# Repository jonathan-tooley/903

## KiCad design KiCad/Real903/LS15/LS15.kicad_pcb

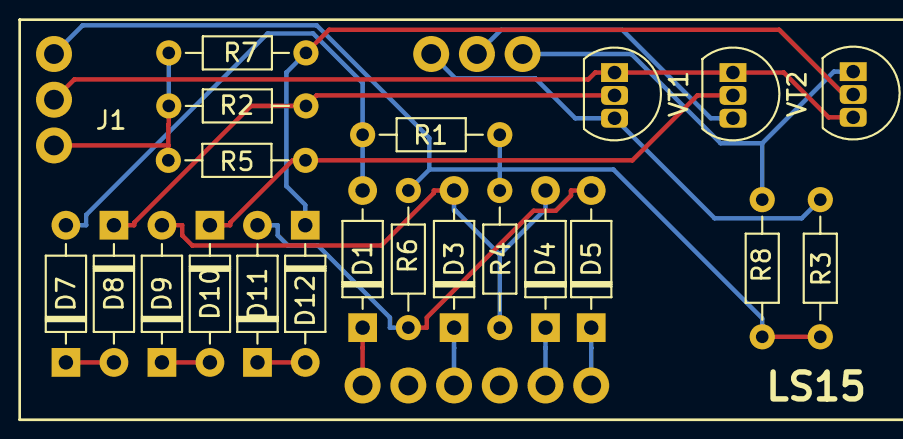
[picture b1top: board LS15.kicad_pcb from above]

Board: 2 copper layers, 22 parts (0 on the bottom side), 19 nets.

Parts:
D1, D3, D4, D5, D7, D8, D9, D10, D11, D12: 1N4148; D_DO-35_SOD27_P7.62mm_Horizontal
J1: LSAConnect; LSA
R1, R6: 1k; R_Axial_DIN0204_L3.6mm_D1.6mm_P7.62mm_Horizontal
R2, R7: 10k; R_Axial_DIN0204_L3.6mm_D1.6mm_P7.62mm_Horizontal
R3, R8: 390R; R_Axial_DIN0204_L3.6mm_D1.6mm_P7.62mm_Horizontal
R4: 2.2k; R_Axial_DIN0204_L3.6mm_D1.6mm_P7.62mm_Horizontal
R5: 22k; R_Axial_DIN0204_L3.6mm_D1.6mm_P7.62mm_Horizontal
VT1: BC548; TO-92L_InlineCBE
VT2, VT3: BC548; TO-92L_Inline

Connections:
0v: J1.22, VT1.3, VT2.3, VT3.3
1: D1.1, J1.1
3: D3.1, J1.3
5: D4.1, J1.5
6: D5.1, J1.6
11: J1.11, R3.1, VT1.1
12: J1.12, VT2.1
13: J1.13, R8.1, VT3.1
+6v: J1.21, R1.1, R3.2, R4.1, R6.1, R8.2
-6v: J1.23, R2.2, R5.2, R7.2
unnamed: D1.2, D7.2, R1.2
unnamed: D3.2, D4.2, D9.2, R4.2
unnamed: D7.1, D8.2
unnamed: D8.1, R2.1, VT1.2
unnamed: D10.1, R5.1, VT2.2
unnamed: D9.1, D10.2
unnamed: D11.1, D12.2
unnamed: D5.2, D11.2, R6.2
unnamed: D12.1, R7.1, VT3.2

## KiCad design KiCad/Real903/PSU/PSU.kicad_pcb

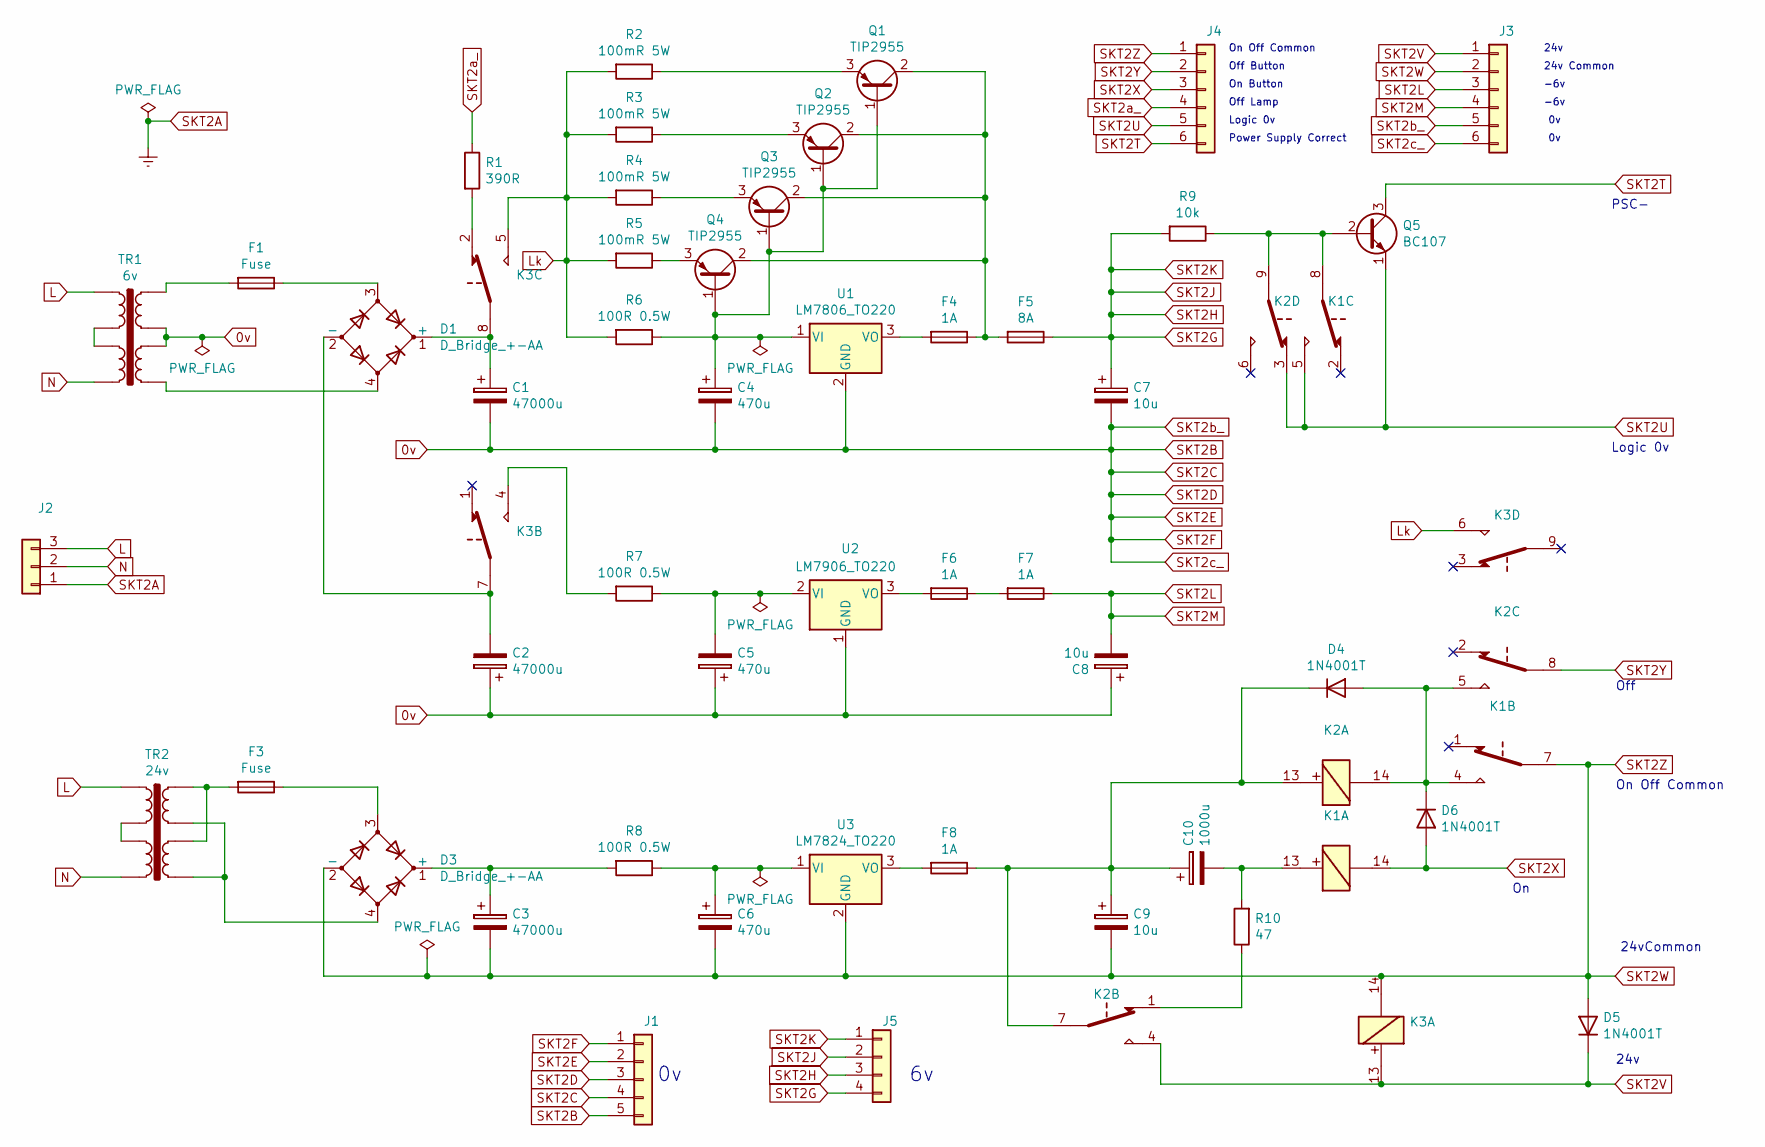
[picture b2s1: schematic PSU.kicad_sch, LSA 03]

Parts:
C1, C2, C3: 47000u; CP_Radial_D35.0mm_P10.00mm_SnapIn
C4, C5, C6: 470u; CP_Radial_D8.0mm_P3.50mm
C7, C8, C9: 10u; CP_Radial_D4.0mm_P1.50mm
C10: 1000u; CP_Radial_D12.5mm_P5.00mm
D1, D3: D_Bridge_+-AA; Diode_Bridge_Vishay_GBU
D4, D5, D6: 1N4001T; D_DO-41_SOD81_P7.62mm_Horizontal
F1, F3: Fuse; TerminalBlock_MetzConnect_Type171_RT13702HBWC_1x02_P7.50mm_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
F4, F6, F7, F8: 1A; TerminalBlock_MetzConnect_Type171_RT13702HBWC_1x02_P7.50mm_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
F5: 8A; TerminalBlock_MetzConnect_Type171_RT13702HBWC_1x02_P7.50mm_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
J1: TerminalBlock_MetzConnect_Type171_RT13705HBWC_1x05_P7.50mm_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
J2: TerminalBlock_MetzConnect_Type171_RT13703HBWC_1x03_P7.50mm_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
J3, J4: TerminalBlock_MetzConnect_Type171_RT13706HBWC_1x06_P7.50mm_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
J5: TerminalBlock_MetzConnect_Type171_RT13704HBWC_1x04_P7.50mm_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
K1, K2, K3: Relay55.13
Q1, Q2, Q3, Q4: TIP2955; TO-218-3_Vertical
Q5: BC107; TO-92L_Inline
R1: 390R; R_Axial_DIN0204_L3.6mm_D1.6mm_P7.62mm_Horizontal
R2, R3, R4, R5: 100mR 5W; R_Axial_Power_L25.0mm_W6.4mm_P27.94mm
R6, R7, R8: 100R 0.5W; R_Axial_DIN0207_L6.3mm_D2.5mm_P2.54mm_Vertical
R9: 10k; R_Axial_DIN0204_L3.6mm_D1.6mm_P7.62mm_Horizontal
R10: 47; R_Axial_DIN0204_L3.6mm_D1.6mm_P7.62mm_Horizontal
TR1: 6v; FL526Transformer
TR2: 24v; FL3024Transformer
U1: LM7806_TO220; TO-220-3_Vertical
U2: LM7906_TO220; TO-220-3_Vertical
U3: LM7824_TO220; TO-220-3_Vertical

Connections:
0v: C1.2, C2.1, C4.2, C5.1, C7.2, C8.1, J1.1, J1.2, J1.3, J1.4, J1.5, J3.5, J3.6, TR1.6, TR1.7, U1.2 (GND), U2.1 (GND)
L: J2.3, TR1.1, TR2.1
Lk: K3.5, K3.6, R2.2, R3.2, R4.2, R5.2, R6.2
N: J2.2, TR1.4, TR2.4
unnamed: C1.1, D1.1 (+), K3.8
unnamed: C2.2, D1.2 (-), K3.7
unnamed: C3.1, D3.1 (+), R8.2
unnamed: C4.1, Q1.1 (B), Q2.1 (B), Q3.1 (B), Q4.1 (B), R6.1, U1.1 (VI)
unnamed: C5.2, R7.1, U2.2 (VI)
unnamed: C6.1, R8.1, U3.1 (VI)
unnamed: C9.1, C10.1, D4.1 (K), F8.1, K2.7, K2.13
unnamed: C10.2, K1.13, R10.2
unnamed: D1.3, F1.1
unnamed: D3.3, F3.1
unnamed: D3.4, TR2.5, TR2.7
unnamed: D4.2 (A), D6.1 (K), K1.4, K2.5, K2.14
unnamed: F1.2, TR1.8
unnamed: F3.2, TR2.6, TR2.8
unnamed: F4.1, F5.2, Q1.2 (C), Q2.2 (C), Q3.2 (C), Q4.2 (C)
unnamed: F4.2, U1.3 (VO)
unnamed: F6.1, F7.2
unnamed: F6.2, U2.3 (VO)
unnamed: F8.2, U3.3 (VO)
unnamed: K1.8, K2.9, Q5.2 (B), R9.1
unnamed: K2.1, R10.1
unnamed: K3.2, R1.2
unnamed: K3.4, R7.2
unnamed: Q1.3 (E), R2.1
unnamed: Q2.3 (E), R3.1
unnamed: Q3.3 (E), R4.1
unnamed: Q4.3 (E), R5.1
unnamed: TR1.2, TR1.3
unnamed: TR2.2, TR2.3
SKT2G: C7.1, F5.1, J5.1, J5.2, J5.3, J5.4, R9.2
SKT2L: C8.2, F7.1, J3.3, J3.4
SKT2T: J4.6, Q5.3 (C)
SKT2U: J4.5, K1.5, K2.3, Q5.1 (E)
SKT2V: D5.1 (K), J3.1, K2.4, K3.13
SKT2W: C3.2, C6.2, C9.2, D3.2 (-), D5.2 (A), J3.2, J4.1, K1.7, K3.14, U3.2 (GND)
SKT2X: D6.2 (A), J4.3, K1.14
SKT2Y: J4.2, K2.8
SKT2a_: J4.4, R1.1

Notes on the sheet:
-6v
24v
On Off Common
PSC-
Off Lamp
Logic 0v
Power Supply Correct
Off Button
24vCommon
On Button
24v Common
Off

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
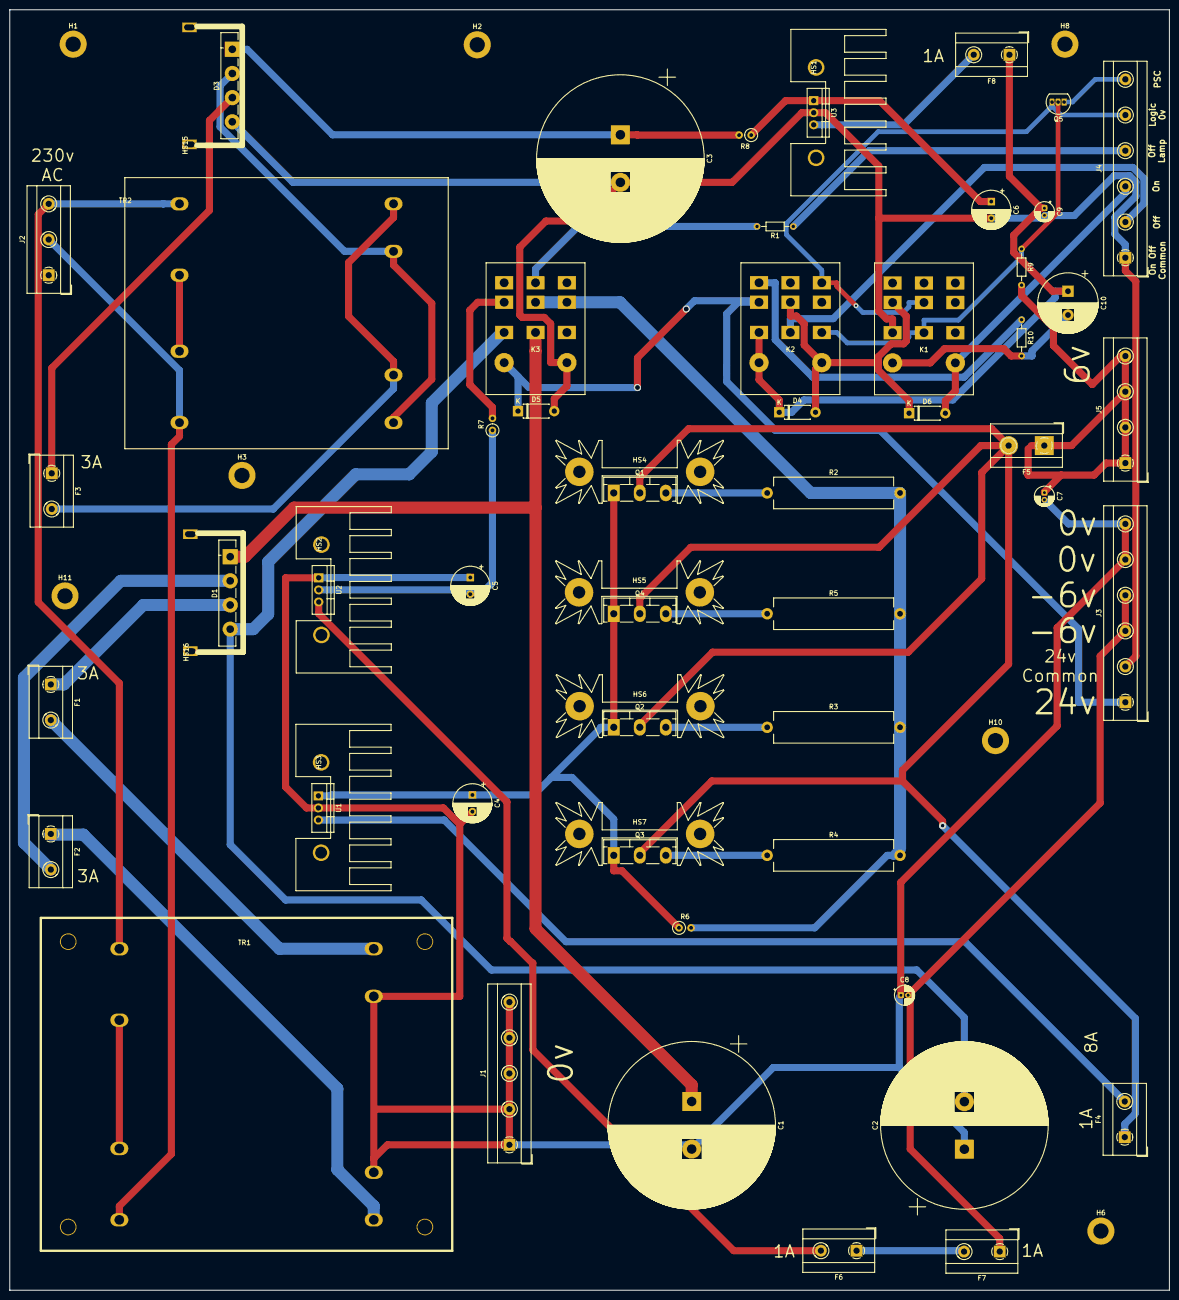
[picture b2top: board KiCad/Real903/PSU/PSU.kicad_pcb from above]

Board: 2 copper layers, 243.8 x 269.2 mm, 67 parts (0 on the bottom side), 44 nets.

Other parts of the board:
F2: Fuse; TerminalBlock_MetzConnect_Type171_RT13702HBWC_1x02_P7.50mm_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
H1, H2, H3, H6, H8, H10, H11: MountingHole_3.2mm_M3_ISO7380_Pad
HS1, HS2, HS3: Heatsink
HS4, HS5, HS6, HS7: Heatsink_TO247
HS15, HS16: Heatsink 712-4241

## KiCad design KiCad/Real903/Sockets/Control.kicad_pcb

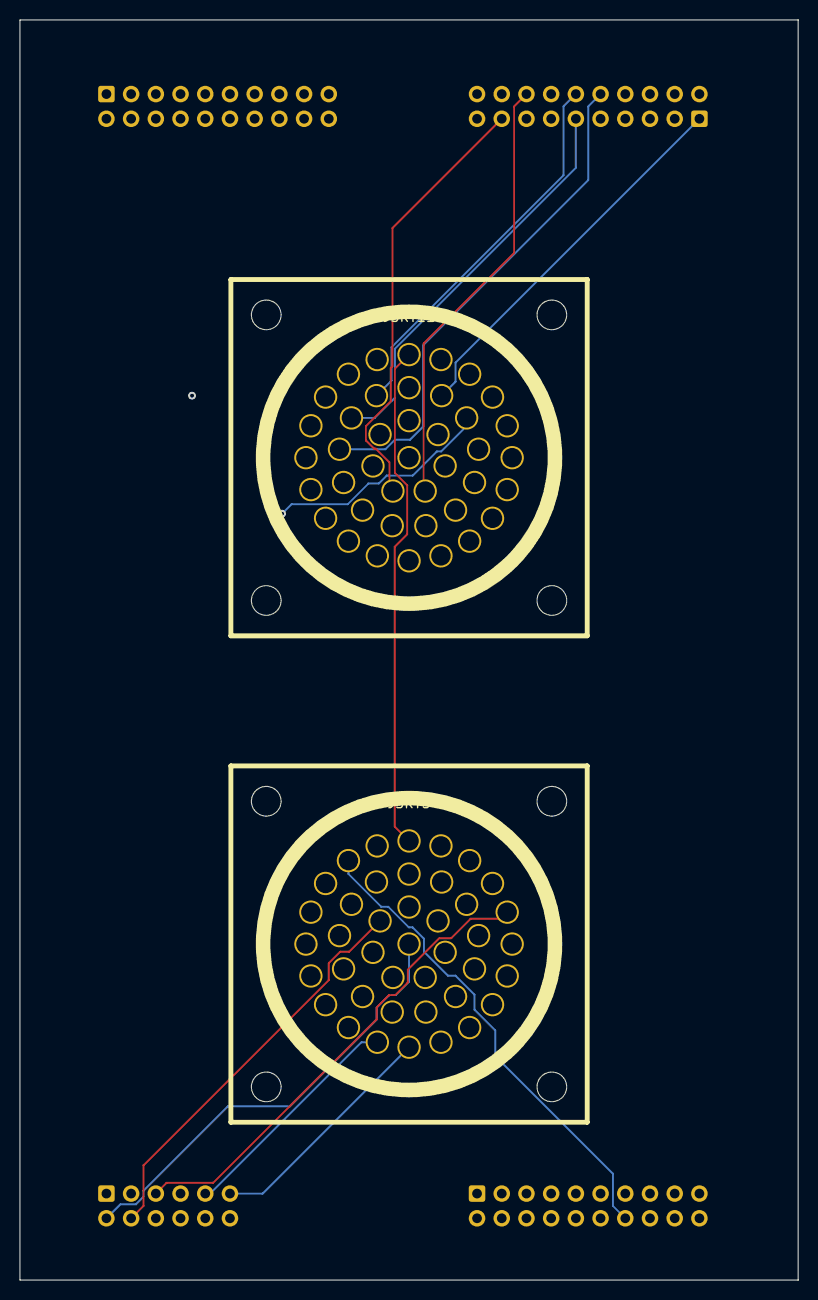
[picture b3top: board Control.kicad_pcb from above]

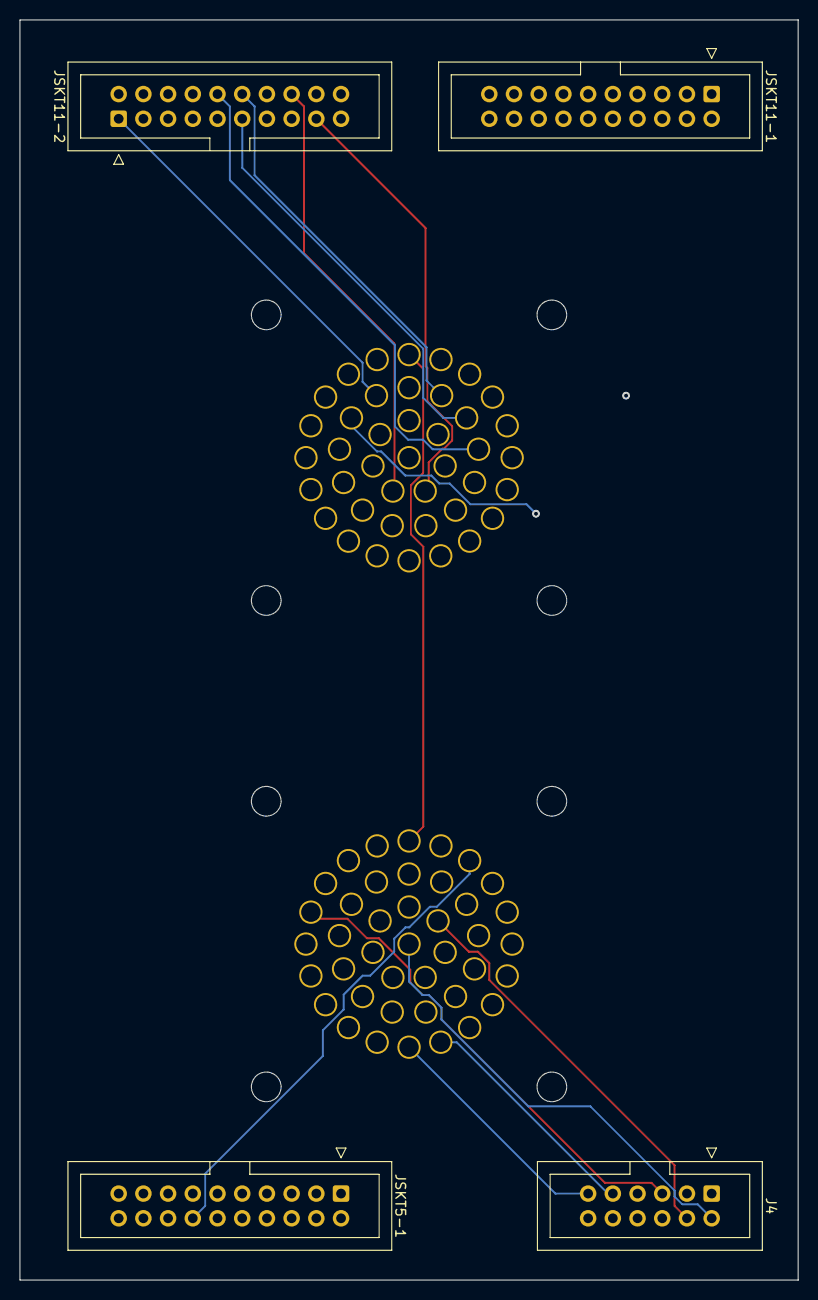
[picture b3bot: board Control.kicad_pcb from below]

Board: 4 copper layers, 80.0 x 129.5 mm, 6 parts (4 on the bottom side), 63 nets.

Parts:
J4: IDC-Header_2x06_P2.54mm_Vertical
JSKT5, JSKT11: Circ41; MC41
JSKT5-1, JSKT11-1, JSKT11-2: IDC-Header_2x10_P2.54mm_Vertical

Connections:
/Control Unit/0v: J4.6, JSKT5.~q~, JSKT5.~r~, JSKT11.~e~
/Control Unit/#ACTIVE1-1-Y: JSKT5.X, JSKT5-1.12
/Control Unit/#ACTIVE2-1-V: JSKT5.Z, JSKT5-1.10
/Control Unit/#ACTIVE3-1-S: JSKT5.~g~, JSKT5-1.3
/Control Unit/#INT1-3-F: JSKT5.Y, JSKT5-1.11
/Control Unit/#INT2-3-W: JSKT5.~a~, JSKT5-1.9
/Control Unit/#INT3-3-AD: JSKT5.~h~, JSKT5-1.2
/Control Unit/#STOP-2-E: JSKT5.R, JSKT5-1.17
/Control Unit/+6v: J4.4, JSKT5.~s~, JSKT11.~t~
/Control Unit/-6v: J4.2, JSKT5.~t~
/Control Unit/AUDIO-32-14: JSKT5.~p~, JSKT11-2.20
/Control Unit/AUT: J4.8, JSKT11.Z
/Control Unit/AUTO-1-L: JSKT5.~k~, JSKT11-2.18
/Control Unit/Auto-Start: J4.10, JSKT11.~r~, JSKT11.~s~
/Control Unit/CINS-1-J: JSKT5.~b~, JSKT5-1.8
/Control Unit/ENG-1-6: JSKT11.~h~, JSKT11-2.10
/Control Unit/INT1-3-9: JSKT11.W, JSKT11-1.19
/Control Unit/INT2-3-10: JSKT11.X, JSKT11-1.20
/Control Unit/INT3-3-11: JSKT11.Y, JSKT11-2.1
/Control Unit/JUMP-1-M: JSKT5.V, JSKT5-1.14
/Control Unit/ONG-1-7: JSKT11.~f~, JSKT11-2.8
/Control Unit/Off: J4.5, JSKT5.E
/Control Unit/Off-Light: J4.11, JSKT5.L
/Control Unit/On: J4.3, JSKT5.B
/Control Unit/On-Light: J4.9, JSKT5.M
/Control Unit/On-Off-Common: J4.7, JSKT5.C
/Control Unit/PS1-3-E: JSKT11.~m~, JSKT11-2.14
/Control Unit/PS2-3-L: JSKT11.~n~, JSKT11-2.15
/Control Unit/PS3-3-S: JSKT11.~p~, JSKT11-2.16
/Control Unit/RESET-1-24: JSKT11.~j~, JSKT11-2.12
/Control Unit/RESET-2-U: JSKT5.H, JSKT5-1.19
/Control Unit/RESTART-1-C: JSKT5.T, JSKT5-1.16
/Control Unit/W1: JSKT11.B, JSKT11-1.1
/Control Unit/W5: JSKT11.F, JSKT11-1.2
/Control Unit/W6: JSKT11.G, JSKT11-1.3
/Control Unit/W7: JSKT11.H, JSKT11-1.4
/Control Unit/W8: JSKT11.J, JSKT11-1.5
/Control Unit/W9: JSKT11.K, JSKT11-1.6
/Control Unit/W10: JSKT11.L, JSKT11-1.7
/Control Unit/W11: JSKT11.M, JSKT11-1.8
/Control Unit/W12: JSKT11.N, JSKT11-1.9
/Control Unit/W13: JSKT11.P, JSKT11-1.10
/Control Unit/W17: JSKT11.~q~, JSKT11-2.17
/Control Unit/~CINS~-1-8: JSKT5.~c~, JSKT5-1.7
/Control Unit/~CS~-1-H: JSKT5.~e~, JSKT5-1.5
/Control Unit/~ENG~-1-4: JSKT11.~i~, JSKT11-2.11
/Control Unit/~JUMP~-1-11: JSKT5.W, JSKT5-1.13
/Control Unit/~ONG~-1-F: JSKT11.~g~, JSKT11-2.9
/Control Unit/~OS~-1-19: JSKT5.~f~, JSKT5-1.4
/Control Unit/~RESTART~-1-3: JSKT5.U, JSKT5-1.15
/Control Unit/~SMN~-4-7: JSKT5.~i~, JSKT5-1.1
/Control Unit/~STOP~-1-25: JSKT5.P, JSKT5-1.18
/Control Unit/~TCS~-1-AB: JSKT5.~d~, JSKT5-1.6
/Control Unit/~TEST~-1-5: JSKT5.D, JSKT5-1.20
/Control Unit/~W~2: JSKT11.C, JSKT11-1.11
/Control Unit/~W~3: JSKT11.D, JSKT11-1.12
/Control Unit/~W~4: JSKT11.E, JSKT11-1.13
/Control Unit/~W~14: JSKT11.R, JSKT11-1.14
/Control Unit/~W~15: JSKT11.S, JSKT11-1.15
/Control Unit/~W~16: JSKT11.T, JSKT11-1.16
/Control Unit/~W~17: JSKT11.U, JSKT11-1.17
/Control Unit/~W~18: JSKT11.V, JSKT11-1.18
GND: J4.1, J4.12, JSKT5.A, JSKT11.A

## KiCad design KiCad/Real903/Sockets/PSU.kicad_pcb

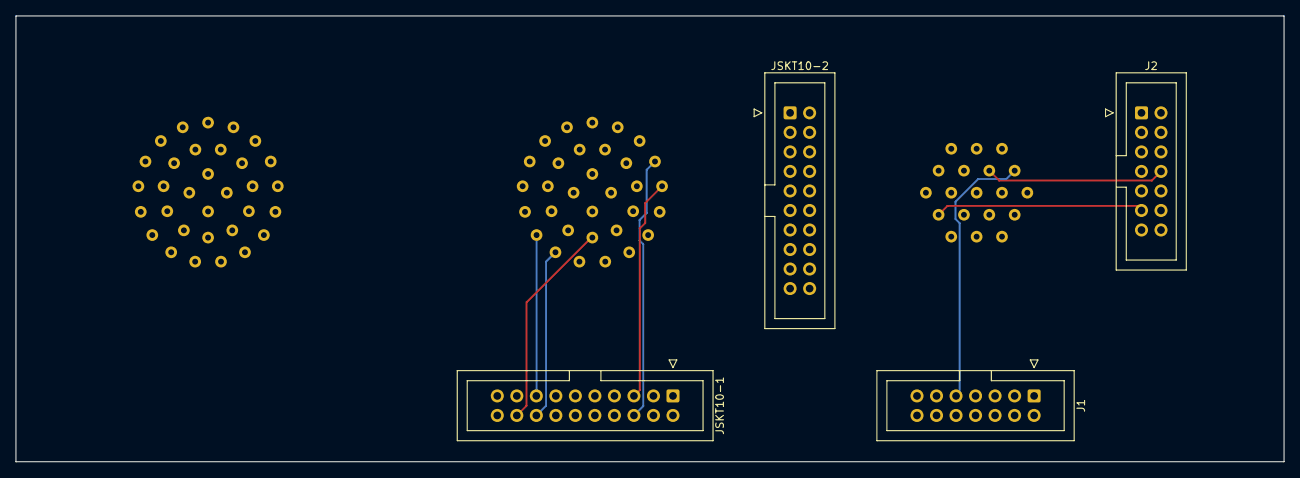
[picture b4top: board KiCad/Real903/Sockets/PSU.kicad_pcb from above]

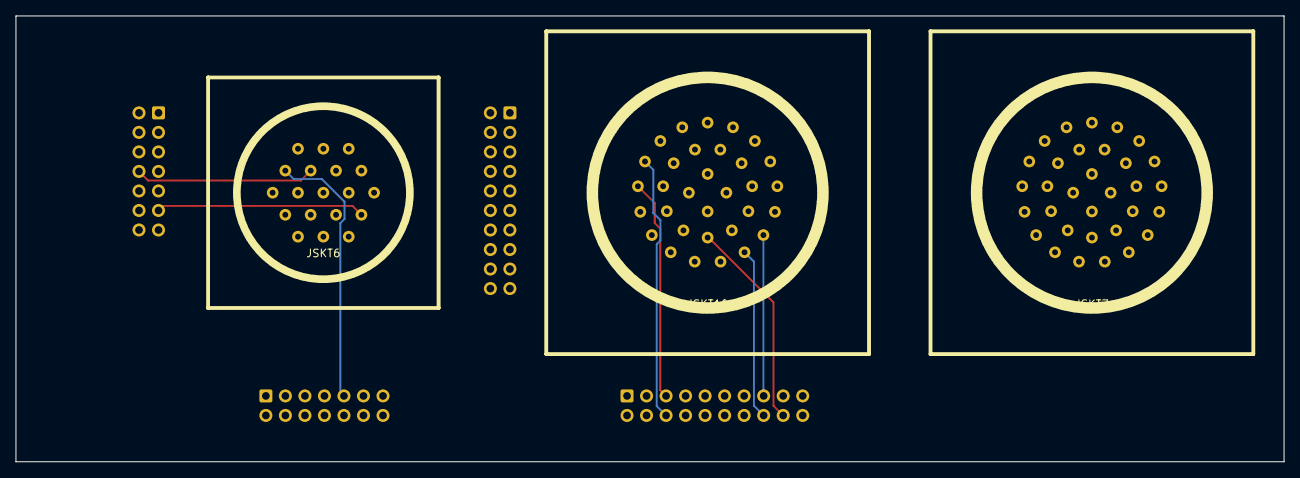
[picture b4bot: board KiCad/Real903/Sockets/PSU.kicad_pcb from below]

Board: 4 copper layers, 165.0 x 58.0 mm, 7 parts (3 on the bottom side), 44 nets.

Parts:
J1, J2: IDC-Header_2x07_P2.54mm_Vertical
JSKT6: Circ19; MC19
JSKT7, JSKT10: Circ32; MC32
JSKT10-1, JSKT10-2: IDC-Header_2x10_P2.54mm_Vertical

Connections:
/Control Unit/0v: J2.9, JSKT6.D, JSKT7.G
/Control Unit/+6v: J1.7, J2.11, JSKT6.L
/Control Unit/-6v: J1.6, J1.8, J2.13, JSKT6.P, JSKT7.B, JSKT7.C, JSKT7.D
/Control Unit/AUT: J2.5, JSKT10.Z
/Control Unit/Auto-Start: J2.7, JSKT6.B
/Control Unit/Off: J2.14, JSKT6.K
/Control Unit/Off-Light: J2.6, JSKT6.T
/Control Unit/On: J2.12, JSKT6.J
/Control Unit/On-Light: J2.8, JSKT6.S
/Control Unit/On-Off-Common: J2.10, JSKT6.H
/Display/0vDisplay: J2.4, JSKT6.U
/Display/+5vDisplay: J2.2, JSKT6.V
/TapePSUMargins/0vA: J1.9, JSKT6.E
/TapePSUMargins/0vB: J1.11, JSKT6.F
/TapePSUMargins/0vC: J1.13, JSKT6.G
/TapePSUMargins/+6vA: J1.3, JSKT6.N
/TapePSUMargins/+6vB: J1.5, JSKT6.M
/TapePSUMargins/-6vA: J1.4, JSKT6.R
/TapePSUMargins/MARGIN-4-3: JSKT7.K, JSKT10-1.20
/TapePSUMargins/MARGIN-25-12: JSKT7.L, JSKT10-2.20
/TapePSUMargins/MARGIN-30-10: JSKT7.J, JSKT10-1.19
/TapePSUMargins/P1-32-17: JSKT10.X, JSKT10-2.12
/TapePSUMargins/P2-32-15: JSKT10.Y, JSKT10-2.11
/TapePSUMargins/P3-32-18: JSKT10.U, JSKT10-1.18
/TapePSUMargins/RTR-30-D: JSKT10.W, JSKT10-2.13
/TapePSUMargins/STR-30-14: JSKT10.V, JSKT10-2.14
/TapePSUMargins/VREF: J1.10, JSKT7.F
GND: J1.12, J1.14, JSKT6.A, JSKT7.A, JSKT10.T
unnamed: JSKT10.A, JSKT10-1.1
unnamed: JSKT10.B, JSKT10-1.2
unnamed: JSKT10.C, JSKT10-1.3
unnamed: JSKT10.D, JSKT10-1.4
unnamed: JSKT10.E, JSKT10-1.5
unnamed: JSKT10.F, JSKT10-1.6
unnamed: JSKT10.G, JSKT10-1.7
unnamed: JSKT10.H, JSKT10-1.8
unnamed: JSKT10.J, JSKT10-1.9
unnamed: JSKT10.K, JSKT10-1.10
unnamed: JSKT10.L, JSKT10-1.11
unnamed: JSKT10.M, JSKT10-1.12
unnamed: JSKT10.N, JSKT10-1.13
unnamed: JSKT10.P, JSKT10-1.14
unnamed: JSKT10.R, JSKT10-1.15
unnamed: JSKT10.S, JSKT10-1.16

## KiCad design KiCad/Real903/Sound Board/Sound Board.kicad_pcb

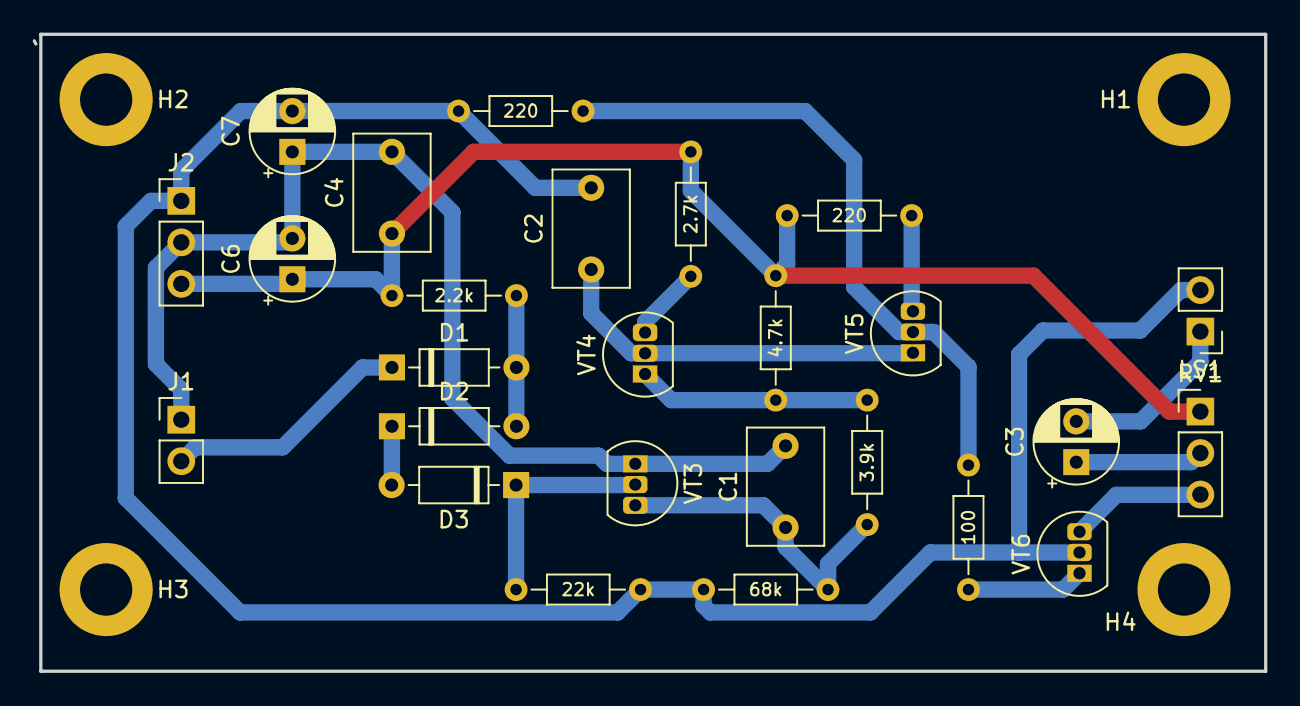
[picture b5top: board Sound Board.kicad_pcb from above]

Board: 2 copper layers, 75.0 x 39.0 mm, 30 parts (0 on the bottom side), 17 nets.

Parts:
C1, C4: 0.1; C_Rect_L7.0mm_W4.5mm_P5.00mm
C2: .068; C_Rect_L7.0mm_W4.5mm_P5.00mm
C3: 10; CP_Radial_D5.0mm_P2.50mm
C6, C7: 6.8; CP_Radial_D5.0mm_P2.50mm
D1, D2, D3: 1N4148; D_DO-35_SOD27_P7.62mm_Horizontal
H1, H2, H3, H4: MountingHole_3.2mm_M3_ISO7380_Pad
J1: Conn_01x02; PinHeader_1x02_P2.54mm_Vertical
J2: Conn_01x03; PinHeader_1x03_P2.54mm_Vertical
LS1: Speaker; PinHeader_1x02_P2.54mm_Vertical
R10: 2.2k; R_Axial_DIN0204_L3.6mm_D1.6mm_P7.62mm_Horizontal
R11: 22k; R_Axial_DIN0204_L3.6mm_D1.6mm_P7.62mm_Horizontal
R12: 4.7k; R_Axial_DIN0204_L3.6mm_D1.6mm_P7.62mm_Horizontal
R13: 3.9k; R_Axial_DIN0204_L3.6mm_D1.6mm_P7.62mm_Horizontal
R14: 68k; R_Axial_DIN0204_L3.6mm_D1.6mm_P7.62mm_Horizontal
R15: 2.7k; R_Axial_DIN0204_L3.6mm_D1.6mm_P7.62mm_Horizontal
R16, R17: 220; R_Axial_DIN0204_L3.6mm_D1.6mm_P7.62mm_Horizontal
R18: 100; R_Axial_DIN0204_L3.6mm_D1.6mm_P7.62mm_Horizontal
RV1: 50; PinHeader_1x03_P2.54mm_Vertical
VT3: BC548; TO-92L_Inline
VT4, VT5, VT6: TO-92L_Inline

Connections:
0v: C1.2, C4.2, C6.2, C7.1, J1.1, J2.2, VT3.1
+6v: C4.1, C6.1, J2.3, R10.1, R12.2, R15.1, R16.1, RV1.1
-6v: C2.2, C7.2, J2.1, LS1.2, R11.2, R14.2, R17.2, VT6.2
AudioIn: D1.1, J1.2
unnamed: C1.1, R13.2, R14.1, VT3.3
unnamed: C2.1, VT4.2, VT5.1
unnamed: C3.1, RV1.2
unnamed: C3.2, LS1.1
unnamed: D1.2, D2.2, R10.2
unnamed: D2.1, D3.2
unnamed: D3.1, R11.1, VT3.2
unnamed: R12.1, R13.1, VT4.1
unnamed: R15.2, VT4.3
unnamed: R16.2, VT5.3
unnamed: R17.1, R18.2, VT5.2
unnamed: R18.1, VT6.1
unnamed: RV1.3, VT6.3

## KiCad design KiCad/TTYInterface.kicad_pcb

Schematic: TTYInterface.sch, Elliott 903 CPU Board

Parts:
C1, C2, C3, C4, C5: 100n; C_Rect_L7.2mm_W2.5mm_P5.00mm_FKS2_FKP2_MKS2_MKP2
J1: CONN_02X10; Molex_Microfit3_Header_02x10_Angled_43045-200x
J2: DB25_FEMALE; DSUB-25_Female_Vertical_Pitch2.77x2.84mm_MountingHoles
U1: MAX3232; DIP-16_W7.62mm

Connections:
0V: C3.1, C4.1, C5.1, J1.9, J1.15, J2.7, U1.15 (GND)
+5V: C5.2, J1.7, U1.16 (VCC)
unnamed: C1.1, U1.1 (C1+)
unnamed: C1.2, U1.3 (C1-)
unnamed: C2.1, U1.4 (C2+)
unnamed: C2.2, U1.5 (C2-)
unnamed: C3.2, U1.2 (VS+)
unnamed: C4.2, U1.6 (VS-)
unnamed: J1.17, U1.12 (R1OUT)
unnamed: J1.19, U1.11 (T1IN)
unnamed: J2.2, U1.7 (T2OUT)
unnamed: J2.3, U1.13 (R1IN)

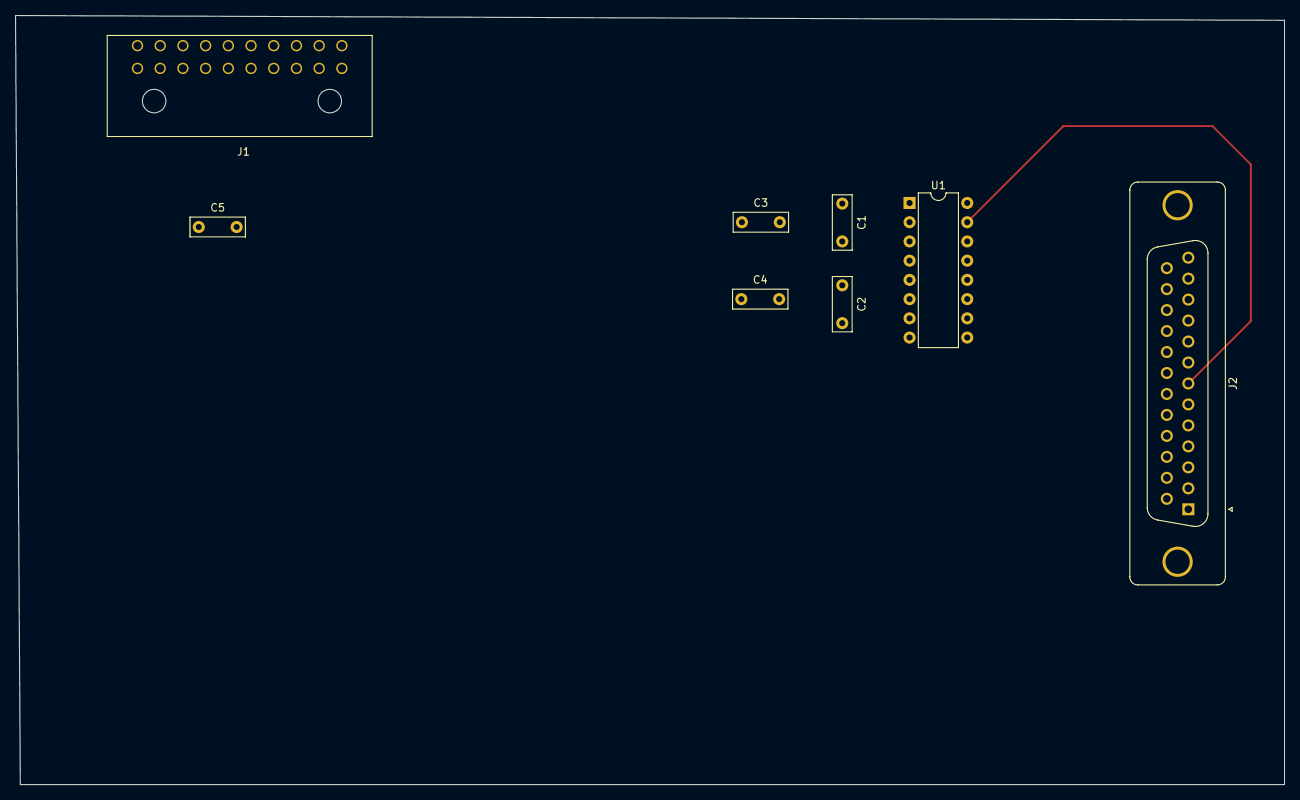
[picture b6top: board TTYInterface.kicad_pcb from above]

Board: 2 copper layers, 167.6 x 101.6 mm, 8 parts (0 on the bottom side), 12 nets.
